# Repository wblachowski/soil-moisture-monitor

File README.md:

# Soil Moisture Monitor 🌱
> There's no reason to stick your finger in the dirt ever again.

This is an Arduino project for monitoring soil moisture to keep your plants lush and healthy. It comes with a standard moisture reading as well as automatic watering detection to let you know how long it's been since the last watering.

## Components
Originally, the project uses the following components (albeit many of these could be substituted with their counterparts without much effort):
* Arduino Nano
* LM393 Soil moisture sensor
* DS3231 RTC
* SSD1306 128x32 OLED Display

## Usage
The main aim of the monitor is to display the soil moisture to the user. However, there are a few add-ons to make the experience even better.

### Moisture sensing
The moisture is measured every minute by supplying the power to the sensor for 50ms and taking the measurement. The measurement in 0-100% format is then displayed in large font in the left part fo the display.

The reason for taking measurements at intervals instead of continuously is to slow down the sensor rusting (some rusting can't be prevented, sadly).

### Watering detection
The system measures the Exponential Moving Average of the sensor measurements and keeps track of the latest 30 values.
Based on some thresholds, the monitor detects whether a significant increase in the moisture has occurred.
Once watering is detected, the system saves the watering time in its non-volatile memory and, henceforth, displays the time that has passed since the last watering on the right-hand side of the display.
A new watering can't be detected until at least 3 hours since the last one.
This behaviour aims to prevent multiple watering events from being detected if the moisture level keeps raising for an extended period of time after the actual watering.

### Watering triggering
If the user feels uncertain about the automatic watering detection mechanism, they can let the system know that the watering has happened by pressing a special button and holding it for 2 seconds.
This event is treated in the same way as the automatic detection.

## Structure

* `main`

Contains arduino code.

* `pcb`

Contains designs for a printed circuit board, created in Autodesk EAGLE.

* `case`

Contains the design of a 3D-printable case for the complete project. The case has snap joints and special cutouts for LCD, power supply, and moisture sensor connection.

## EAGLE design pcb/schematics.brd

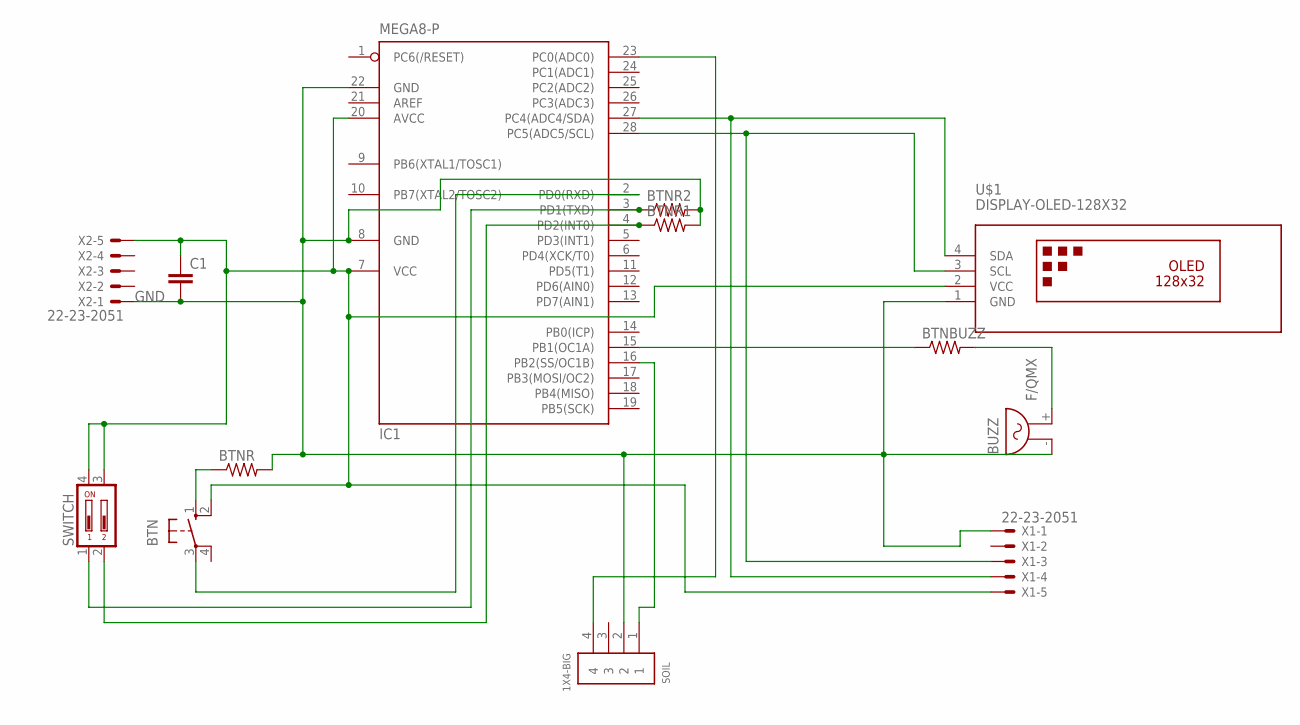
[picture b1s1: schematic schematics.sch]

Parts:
BTN: 10-XX; B3F-10XX
BTNBUZZ: R-US_0204/7; 0204/7
BTNR, BTNR1, BTNR2: R-US_0204/7; 0204/7
BUZZ: F/QMX
C1: C-EU025-025X050; C025-025X050
IC1: MEGA8-P; DIL28-3
SOIL: 1X4-BIG; 1X04-BIG
SWITCH: DIP02YL
U$1: DISPLAY-OLED-128X32
X1, X2: 22-23-2051

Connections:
GND: BTNR.2, BTNR1.2, BTNR2.2, BUZZ.- (1), C1.2, IC1.8 (GND), IC1.22 (GND), SOIL.2, U$1.1 (GND), X1.1, X2.1
unnamed: IC1.27 (PC4(ADC4/SDA)), U$1.4 (SDA), X1.4
unnamed: IC1.28 (PC5(ADC5/SCL)), U$1.3 (SCL), X1.3
unnamed: BTNR2.1, IC1.3 (PD1(TXD)), SWITCH.1
unnamed: BTNBUZZ.1, IC1.15 (PB1(OC1A))
unnamed: BTN.2 (S1), C1.1, IC1.7 (VCC), IC1.20 (AVCC), SWITCH.3, SWITCH.4, U$1.2 (VCC), X1.5, X2.5
unnamed: IC1.16 (PB2(SS/OC1B)), SOIL.1
unnamed: BTN.1 (S), BTNR.1
unnamed: BTN.3, IC1.2 (PD0(RXD))
unnamed: IC1.23 (PC0(ADC0)), SOIL.4
unnamed: BTNR1.1, IC1.4 (PD2(INT0)), SWITCH.2
unnamed: BTNBUZZ.2, BUZZ.+ (2)

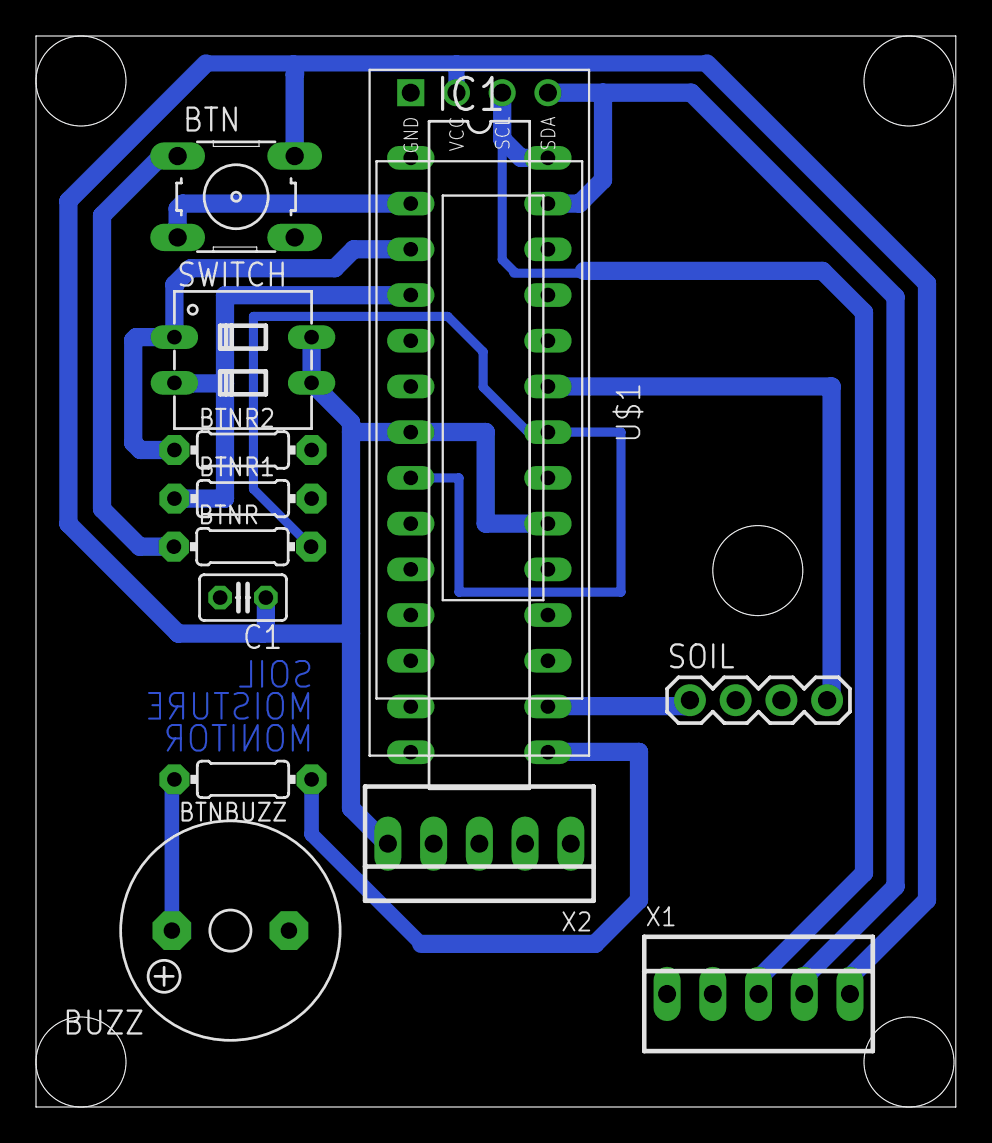
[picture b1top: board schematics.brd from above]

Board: 2 copper layers, 51.1 x 59.5 mm, 13 parts (0 on the bottom side), 12 nets.

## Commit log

2021-02-02 Add main file
2021-02-02 Remove delay
2021-02-03 Fixes
2021-02-08 Add powering the sensor once every minute
2021-02-09 Add displaying time
2021-02-09 Refactoring (create a separate Display class)
2021-02-09 Refactoring
2021-02-09 Refactoring (reduce loop length)
2021-02-10 Add measurement history buffer
2021-02-10 Implement EMA as history inputs
2021-02-10 Implement watering detection
2021-02-10 Check whether the buffer is full while detecting watering
2021-02-10 Change last watering storing to RTC
2021-02-10 Add watering detection notebook
2021-02-10 Add gitignore
2021-02-10 Refactor include statement
2021-02-10 Add saving/reading last watering
2021-02-10 Fix notebook issues
2021-02-10 Add displaying last watering time
2021-02-10 Ensure percentage is always two-digit
2021-02-11 Fix displaying watering
2021-02-12 Refactor cyclic execution of things
2021-02-12 Add rudimentary button handling
2021-02-12 Extract button related logic
2021-02-12 Add displaying button press time
2021-02-12 Add disabling button handler upon reaching the threshold
2021-02-12 Add watering on button press + refactor
2021-02-12 Add findings
2021-02-12 Update measurement duration constant
2021-02-12 Remove unneeded headers
2021-02-12 Update plots
2021-02-12 Reorganize the code
2021-02-12 Reorganize constants
2021-02-15 Add button debouncing
2021-02-15 Fix screen flicker on watering
2021-02-17 Change sensor (reverse logic)
2021-02-17 Add buzzer
2021-02-17 Add buzz on start
2021-02-18 Update debounce comment
2021-02-20 Change constants
2021-03-02 Revert to the previous sensor
2021-03-02 Change watering detection thresholds
2021-03-08 Add buzz to watering reaction
2021-03-17 Fix header size
2021-03-30 Add pcb files
2021-03-31 Update pcb
2021-04-13 Update eagle files
2021-04-14 Update eagle files (shrinking the board)
2021-04-14 Change button pin
2021-04-14 Add changing display orientation
2021-04-14 Add conditional buzzing
2021-04-14 Add changing display rotatio dynamically
2021-04-14 Add slide switch
2021-04-19 Update pcb schematics to its final form
2021-05-03 Upadate pcb to use passive buzzer
2021-05-03 Change buzzer to pasive
2021-05-10 Add image of the board
2021-05-10 Add case files

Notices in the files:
parts and their libraries:
diy-modules: Released under the Creative Commons Attribution 4.0 International License: http://creativecommons.org/licenses/by/4.0
